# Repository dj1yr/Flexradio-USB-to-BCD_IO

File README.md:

Since Flexradio does not output any band data from the device, the Flexwire bus unfortunately does not work. (is not implemented by Flex)
I have created a circuit board which adapts the USB signal to TTL to the Arduino Every.
The Flexradio only recognizes FTDI converters!
The board has BCD out, TXin and TXout, as well as 16 I/O via PCF8575 for other functions.
I need the board to control my VL-1000.

The software is currently under development and so far only reads and selects the data.

73' René

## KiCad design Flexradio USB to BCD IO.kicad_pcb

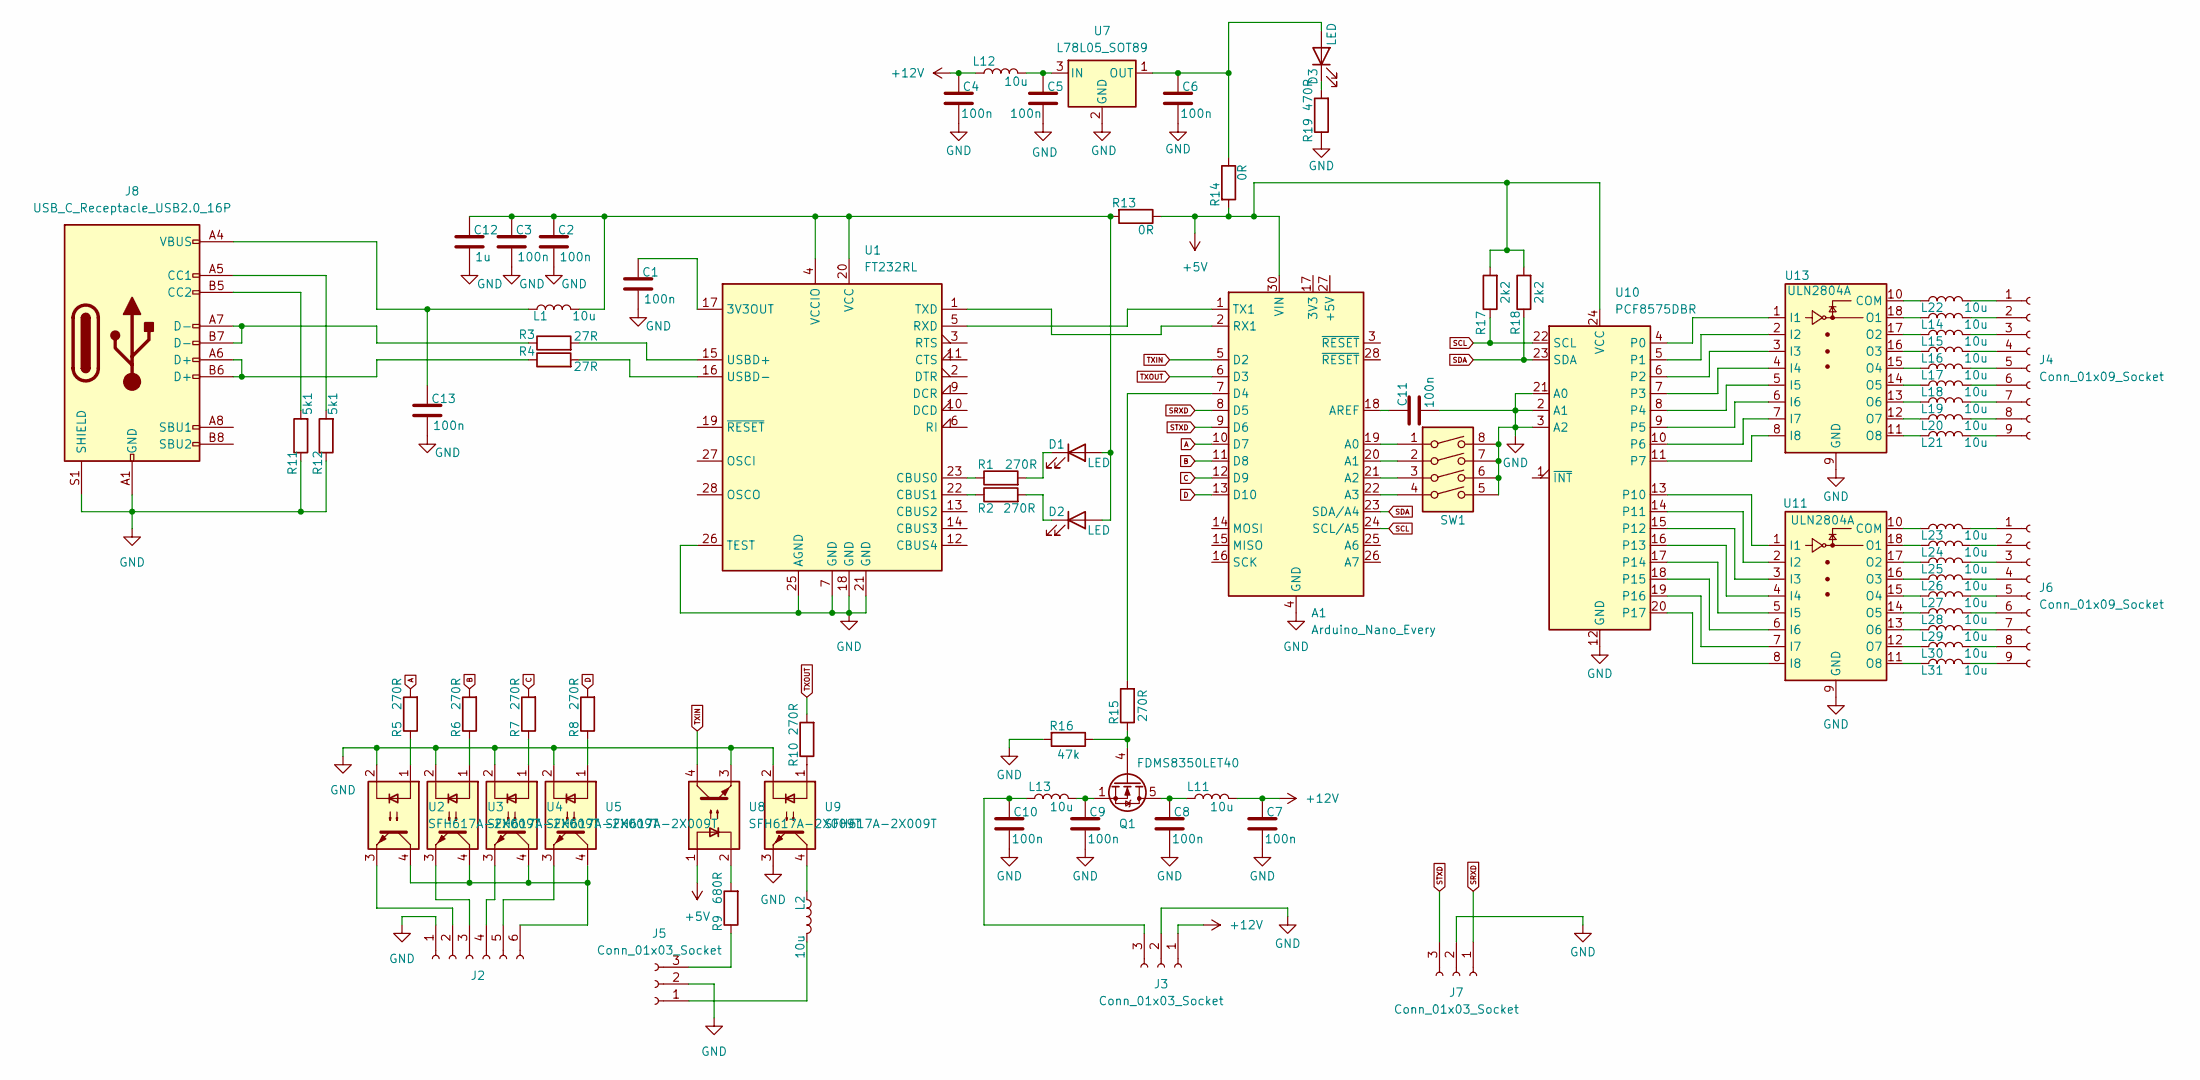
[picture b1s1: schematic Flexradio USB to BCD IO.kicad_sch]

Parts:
A1: Arduino_Nano_Every; Arduino_Nano
C1, C2, C3, C4, C5, C6, C7, C8, C9, C10, C11, C13: 100n; C_0805_2012Metric_Pad1.18x1.45mm_HandSolder
C12: 1u; C_0805_2012Metric_Pad1.18x1.45mm_HandSolder
D1, D2, D3: LED; LED_0805_2012Metric
J2: Conn_01x06_Socket; JST_EH_B6B-EH-A_1x06_P2.50mm_Vertical
J3, J5, J7: Conn_01x03_Socket; JST_EH_B3B-EH-A_1x03_P2.50mm_Vertical
J4, J6: Conn_01x09_Socket; JST_EH_B9B-EH-A_1x09_P2.50mm_Vertical
J8: USB_C_Receptacle_USB2.0_16P; USB_C_Receptacle_GCT_USB4105-xx-A_16P_TopMnt_Horizontal
L1, L2, L11, L12, L13, L14, L15, L16, L17, L18, L19, L20, L21, L22, L23, L24, L25, L26, L27, L28, L29, L30, L31: 10u; L_0805_2012Metric_Pad1.15x1.40mm_HandSolder
Q1: FDMS8350LET40; TDSON-8-1
R1, R2, R5, R6, R7, R8, R10, R15: 270R; R_0805_2012Metric_Pad1.20x1.40mm_HandSolder
R3, R4: 27R; R_0805_2012Metric_Pad1.20x1.40mm_HandSolder
R9: 680R; R_0805_2012Metric_Pad1.20x1.40mm_HandSolder
R11, R12: 5k1; R_0805_2012Metric_Pad1.20x1.40mm_HandSolder
R13, R14: 0R; R_0805_2012Metric_Pad1.20x1.40mm_HandSolder
R16: 47k; R_0805_2012Metric_Pad1.20x1.40mm_HandSolder
R17, R18: 2k2; R_0805_2012Metric_Pad1.20x1.40mm_HandSolder
R19: 470R; R_0805_2012Metric_Pad1.20x1.40mm_HandSolder
SW1: SW_DIP_x04; SW_DIP_SPSTx04_Slide_9.78x12.34mm_W7.62mm_P2.54mm
U1: FT232RL; SSOP-28_5.3x10.2mm_P0.65mm
U2, U3, U4, U5, U8, U9: SFH617A-2X009T; SMDIP-4_W7.62mm
U7: L78L05_SOT89; SOT-89-3
U10: PCF8575DBR; SSOP-24_5.3x8.2mm_P0.65mm
U11, U13: ULN2804A; SOIC-18W_7.5x11.6mm_P1.27mm

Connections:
+5V: A1.30 (VIN), R13.1, R14.2, R17.2, R18.2, U8.1, U10.24 (VCC)
+12V: C4.1, C7.1, J3.1, L11.2, L12.1
A: A1.10 (D7), R5.2
B: A1.11 (D8), R6.2
C: A1.12 (D9), R7.2
D: A1.13 (D10), R8.2
GND: A1.4 (GND), A1.29 (GND), C1.2, C2.2, C3.2, C4.2, C5.2, C6.2, C7.2, C8.2, C9.2, C10.2, C11.2, C12.2, C13.2, J2.1, J3.2, J5.2, J7.2, J8.A1 (GND), J8.A12 (GND), J8.B1 (GND), J8.B12 (GND), J8.S1 (SHIELD), R11.1, R12.1, R16.2, R19.1, SW1.5, SW1.6, SW1.7, SW1.8, U1.7 (GND), U1.18 (GND), U1.21 (GND), U1.25 (AGND), U1.26 (TEST), U2.2, U3.2, U4.2, U5.2, U7.2 (GND), U8.3, U9.2, U9.3, U10.2 (A1), U10.3 (A2), U10.12 (GND), U10.21 (A0), U11.9 (GND), U13.9 (GND)
unnamed: A1.19 (A0), SW1.1
unnamed: A1.20 (A1), SW1.2
unnamed: A1.21 (A2), SW1.3
unnamed: A1.22 (A3), SW1.4
unnamed: A1.18 (AREF), C11.1
unnamed: A1.7 (D4), R15.2
unnamed: A1.2 (RX1), U1.1 (TXD)
unnamed: A1.1 (TX1), U1.5 (RXD)
unnamed: C9.1, L13.2, Q1.1 (S), Q1.2 (S), Q1.3 (S)
unnamed: C13.1, J8.A4 (VBUS), J8.A9 (VBUS), J8.B4 (VBUS), J8.B9 (VBUS), L1.1
unnamed: C2.1, C3.1, C12.1, D1.2 (A), D2.2 (A), L1.2, R13.2, U1.4 (VCCIO), U1.20 (VCC)
unnamed: D1.1 (K), R1.2
unnamed: D2.1 (K), R2.2
unnamed: C6.1, D3.2 (A), R14.1, U7.1 (OUT)
unnamed: D3.1 (K), R19.2
unnamed: J2.2, U2.3
unnamed: J2.3, U3.3
unnamed: J2.4, U4.3
unnamed: J2.5, U5.3
unnamed: J2.6, U2.4, U3.4, U4.4, U5.4
unnamed: C10.1, J3.3, L13.1
unnamed: J4.1, L22.2
unnamed: J4.2, L14.2
unnamed: J4.3, L15.2
unnamed: J4.4, L16.2
unnamed: J4.5, L17.2
unnamed: J4.6, L18.2
unnamed: J4.7, L19.2
unnamed: J4.8, L20.2
unnamed: J4.9, L21.2
unnamed: J5.1, L2.2
unnamed: J5.3, R9.1
unnamed: J6.1, L23.2
unnamed: J6.2, L24.2
unnamed: J6.3, L25.2
unnamed: J6.4, L26.2
unnamed: J6.5, L27.2
unnamed: J6.6, L28.2
unnamed: J6.7, L29.2
unnamed: J6.8, L30.2
unnamed: J6.9, L31.2
unnamed: J8.A5 (CC1), R12.2
unnamed: J8.B5 (CC2), R11.2
unnamed: J8.A6 (D+), J8.B6 (D+), R4.1
unnamed: J8.A7 (D-), J8.B7 (D-), R3.1
unnamed: L2.1, U9.4
unnamed: C8.1, L11.1, Q1.5 (D)
unnamed: Q1.4 (G), R15.1, R16.1
unnamed: R5.1, U2.1
unnamed: R6.1, U3.1
unnamed: R7.1, U4.1
unnamed: R8.1, U5.1
unnamed: R9.2, U8.2
unnamed: R10.1, U9.1
unnamed: C1.1, U1.17 (3V3OUT)
unnamed: R1.1, U1.23 (CBUS0)
unnamed: R2.1, U1.22 (CBUS1)
unnamed: R3.2, U1.15 (USBD+)
unnamed: R4.2, U1.16 (USBD-)
unnamed: C5.1, L12.2, U7.3 (IN)
unnamed: U10.4 (P0), U13.1 (I1)
unnamed: U10.5 (P1), U13.2 (I2)
unnamed: U10.6 (P2), U13.3 (I3)
unnamed: U10.7 (P3), U13.4 (I4)
unnamed: U10.8 (P4), U13.5 (I5)
unnamed: U10.9 (P5), U13.6 (I6)
unnamed: U10.10 (P6), U13.7 (I7)
unnamed: U10.11 (P7), U13.8 (I8)
unnamed: U10.13 (P10), U11.1 (I1)
unnamed: U10.14 (P11), U11.2 (I2)
unnamed: U10.15 (P12), U11.3 (I3)
unnamed: U10.16 (P13), U11.4 (I4)
unnamed: U10.17 (P14), U11.5 (I5)
unnamed: U10.18 (P15), U11.6 (I6)
unnamed: U10.19 (P16), U11.7 (I7)
unnamed: U10.20 (P17), U11.8 (I8)
unnamed: L23.1, U11.10 (COM)
unnamed: L24.1, U11.18 (O1)
unnamed: L25.1, U11.17 (O2)
unnamed: L26.1, U11.16 (O3)
unnamed: L27.1, U11.15 (O4)
unnamed: L28.1, U11.14 (O5)
unnamed: L29.1, U11.13 (O6)
unnamed: L30.1, U11.12 (O7)
unnamed: L31.1, U11.11 (O8)
unnamed: L22.1, U13.10 (COM)
unnamed: L14.1, U13.18 (O1)
unnamed: L15.1, U13.17 (O2)
unnamed: L16.1, U13.16 (O3)
unnamed: L17.1, U13.15 (O4)
unnamed: L18.1, U13.14 (O5)
unnamed: L19.1, U13.13 (O6)
unnamed: L20.1, U13.12 (O7)
unnamed: L21.1, U13.11 (O8)
SCL: A1.24 (SCL/A5), R17.1, U10.22 (SCL)
SDA: A1.23 (SDA/A4), R18.1, U10.23 (SDA)
SRXD: A1.8 (D5), J7.1
STXD: A1.9 (D6), J7.3
TXIN: A1.5 (D2), U8.4
TXOUT: A1.6 (D3), R10.2

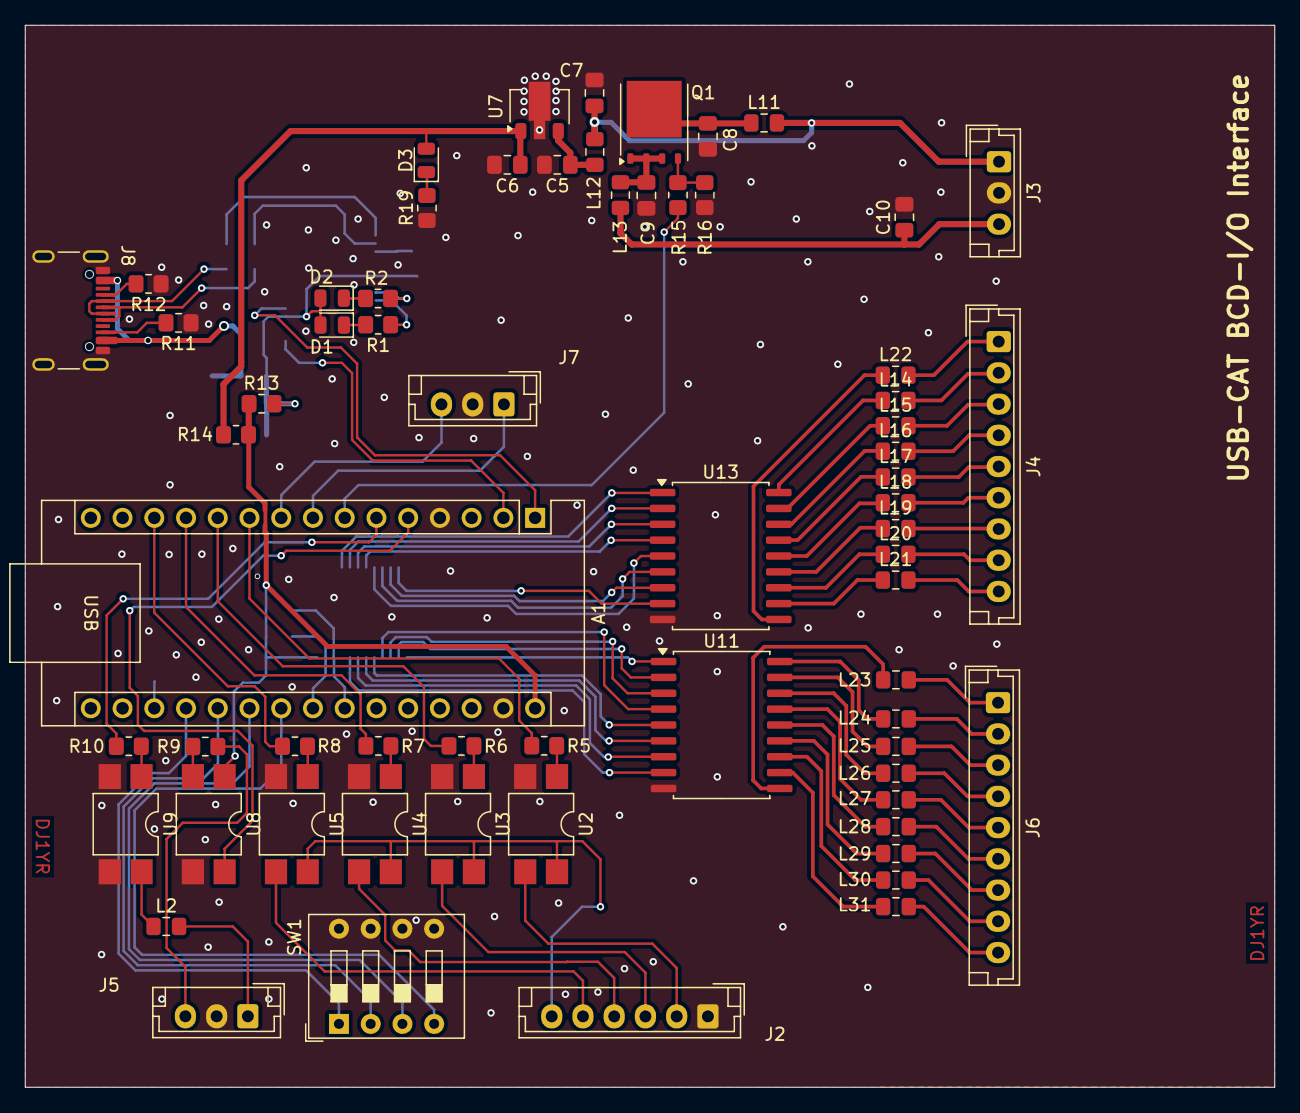
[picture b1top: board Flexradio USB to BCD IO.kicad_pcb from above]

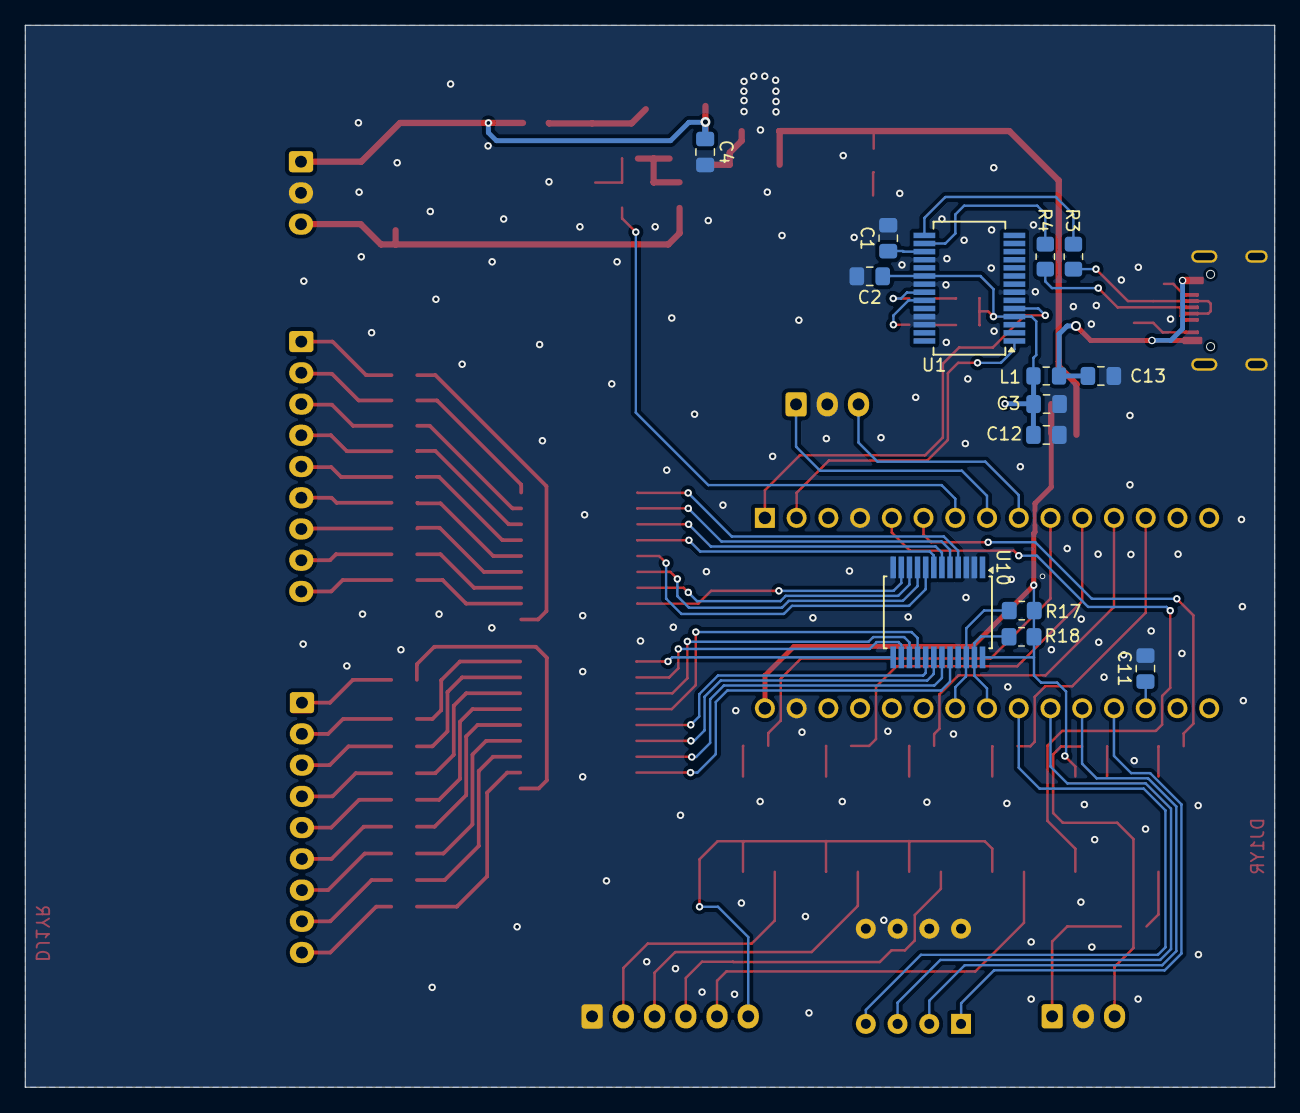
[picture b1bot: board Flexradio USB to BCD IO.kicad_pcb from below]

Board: 2 copper layers, 100.0 x 85.0 mm, 79 parts (14 on the bottom side), 107 nets.
